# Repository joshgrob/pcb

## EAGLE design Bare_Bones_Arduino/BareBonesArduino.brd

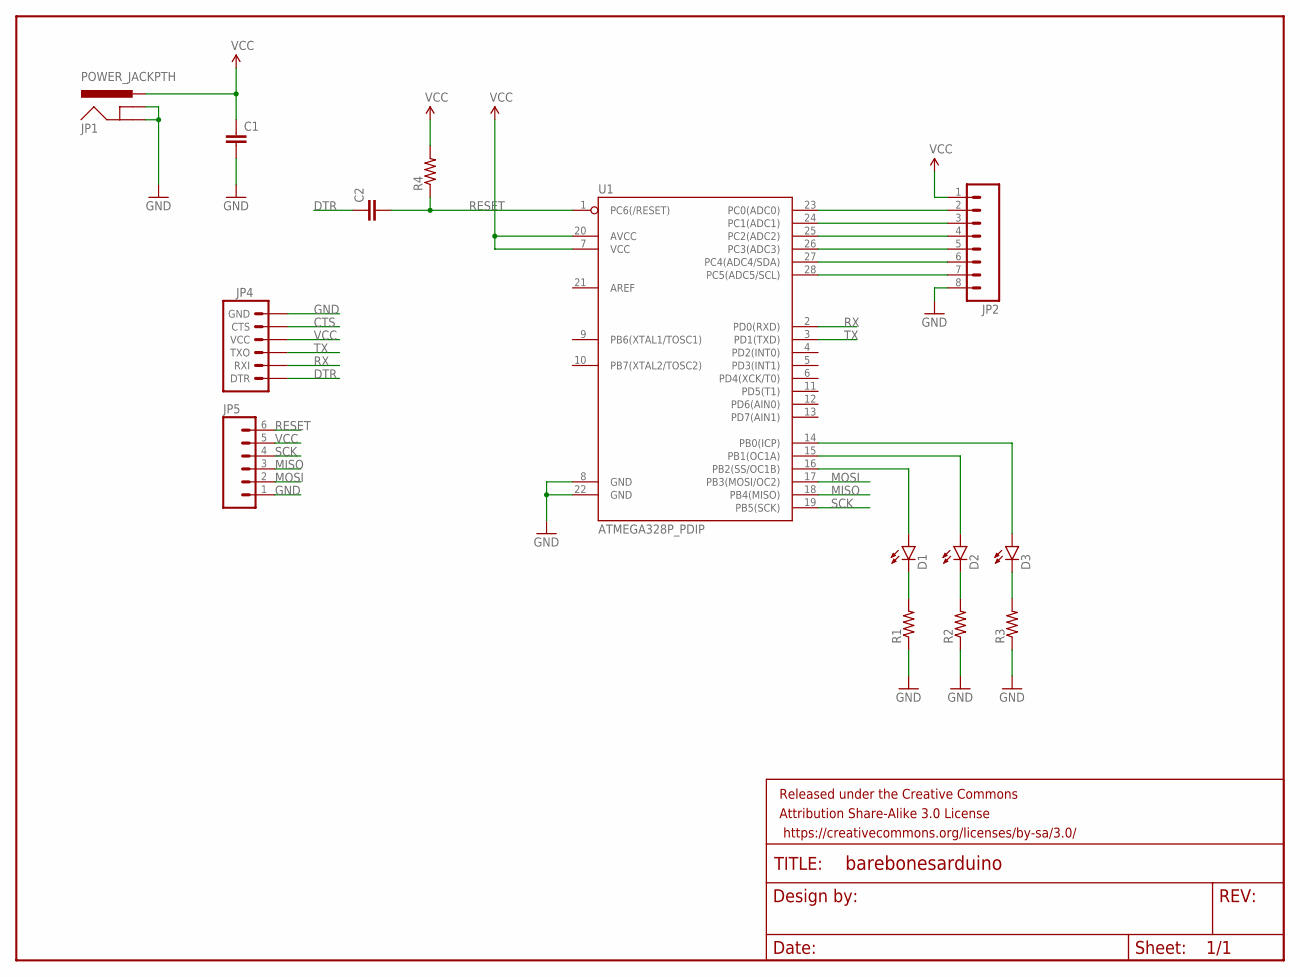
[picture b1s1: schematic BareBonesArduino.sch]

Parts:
C1, C2: CAPPTH; CAP-PTH-SMALL
D1, D2, D3: LED5MM
FRAME1: FRAME-LETTER; CREATIVE_COMMONS
JP1: POWER_JACKPTH; POWER_JACK_PTH
JP2: M08; 1X08_ROUND
JP4: ARDUINO_SERIAL_PROGRAMPTH; 1X06
JP5: M06SILK_FEMALE_PTH; 1X06
R1, R2, R3, R4: RESISTORPTH-1/4W; AXIAL-0.4
U1: ATMEGA328P_PDIP; DIL28-3

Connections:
CTS: JP4.5 (CTS)
DTR: C2.1, JP4.1 (DTR)
GND: C1.2, JP1.GND, JP1.GNDBREAK, JP2.8, JP4.6 (GND), JP5.1, R1.P$1 (1), R2.P$1 (1), R3.P$1 (1), U1.8 (GND), U1.22 (GND)
MISO: JP5.3, U1.18 (PB4(MISO))
MOSI: JP5.2, U1.17 (PB3(MOSI/OC2))
unnamed: D1.K (C), R1.P$2 (2)
unnamed: D2.K (C), R2.P$2 (2)
unnamed: D3.K (C), R3.P$2 (2)
unnamed: D3.A, U1.14 (PB0(ICP))
unnamed: D2.A, U1.15 (PB1(OC1A))
unnamed: D1.A, U1.16 (PB2(SS/OC1B))
unnamed: JP2.2, U1.23 (PC0(ADC0))
unnamed: JP2.3, U1.24 (PC1(ADC1))
unnamed: JP2.4, U1.25 (PC2(ADC2))
unnamed: JP2.5, U1.26 (PC3(ADC3))
unnamed: JP2.6, U1.27 (PC4(ADC4/SDA))
unnamed: JP2.7, U1.28 (PC5(ADC5/SCL))
RESET: C2.2, JP5.6, R4.P$1 (1), U1.1 (PC6(/RESET))
RX: JP4.2 (RXI), U1.2 (PD0(RXD))
SCK: JP5.4, U1.19 (PB5(SCK))
TX: JP4.3 (TXO), U1.3 (PD1(TXD))
VCC: C1.1, JP1.PWR, JP2.1, JP4.4 (VCC), JP5.5, R4.P$2 (2), U1.7 (VCC), U1.20 (AVCC)

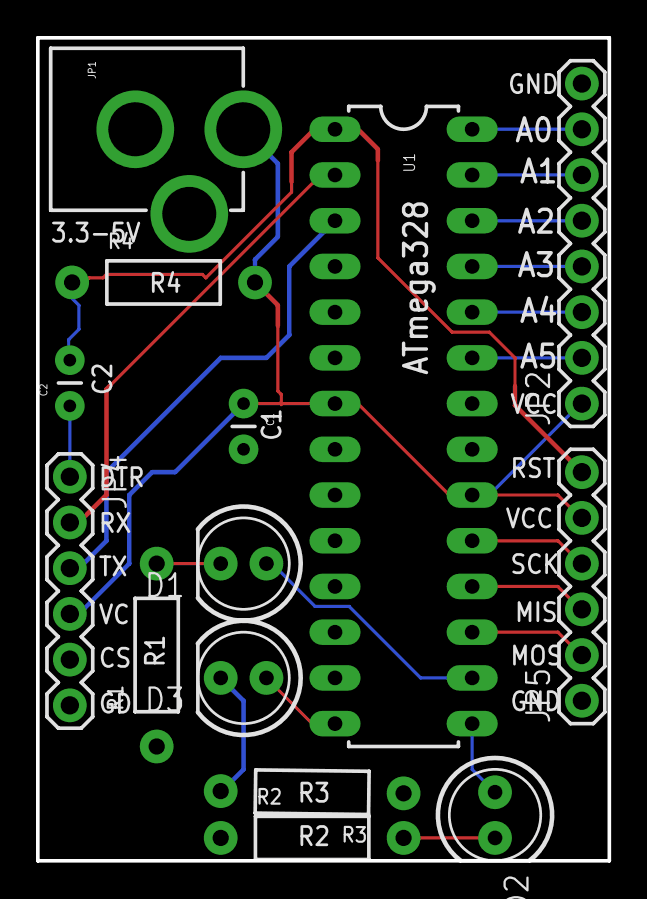
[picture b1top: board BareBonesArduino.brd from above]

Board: 2 copper layers, 31.8 x 45.7 mm, 15 parts (0 on the bottom side), 21 nets.

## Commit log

2015-10-27 Bare Bones Project File
2016-01-01 Version 2 smaller design
2016-01-01 Version 2. Forgot Silks, fix TX/RX

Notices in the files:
parts and their libraries:
SparkFun-Capacitors: Licensing: Creative Commons ShareAlike 4.0 International - https://creativecommons.org/licenses/by-sa/4.0
SparkFun-Retired: Released under the Creative Commons Attribution Share-Alike 3.0 License
SparkFun-Retired: https://creativecommons.org/licenses/by-sa/3.0
